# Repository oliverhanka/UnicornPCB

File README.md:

### UnicornPCB
**Unicorn shaped ESP32 and WS2812b board - CTF hardware**

This PCB has been created as a CTF hardware/badge. It features a Wemos D1 style ESP32 as well as 15 WS2812b LEDs, push button and Seeed Studios's Grove Connector for extentability. Power is obtained form the ESP32 board.

#### Hardware
Open Source Hardware

Frontside of the assembled PCB:

Backside of the assembled PCB:

#### Software
Board test firmware included. Requires ESP32 SDK and Arduino NeoPixel library.

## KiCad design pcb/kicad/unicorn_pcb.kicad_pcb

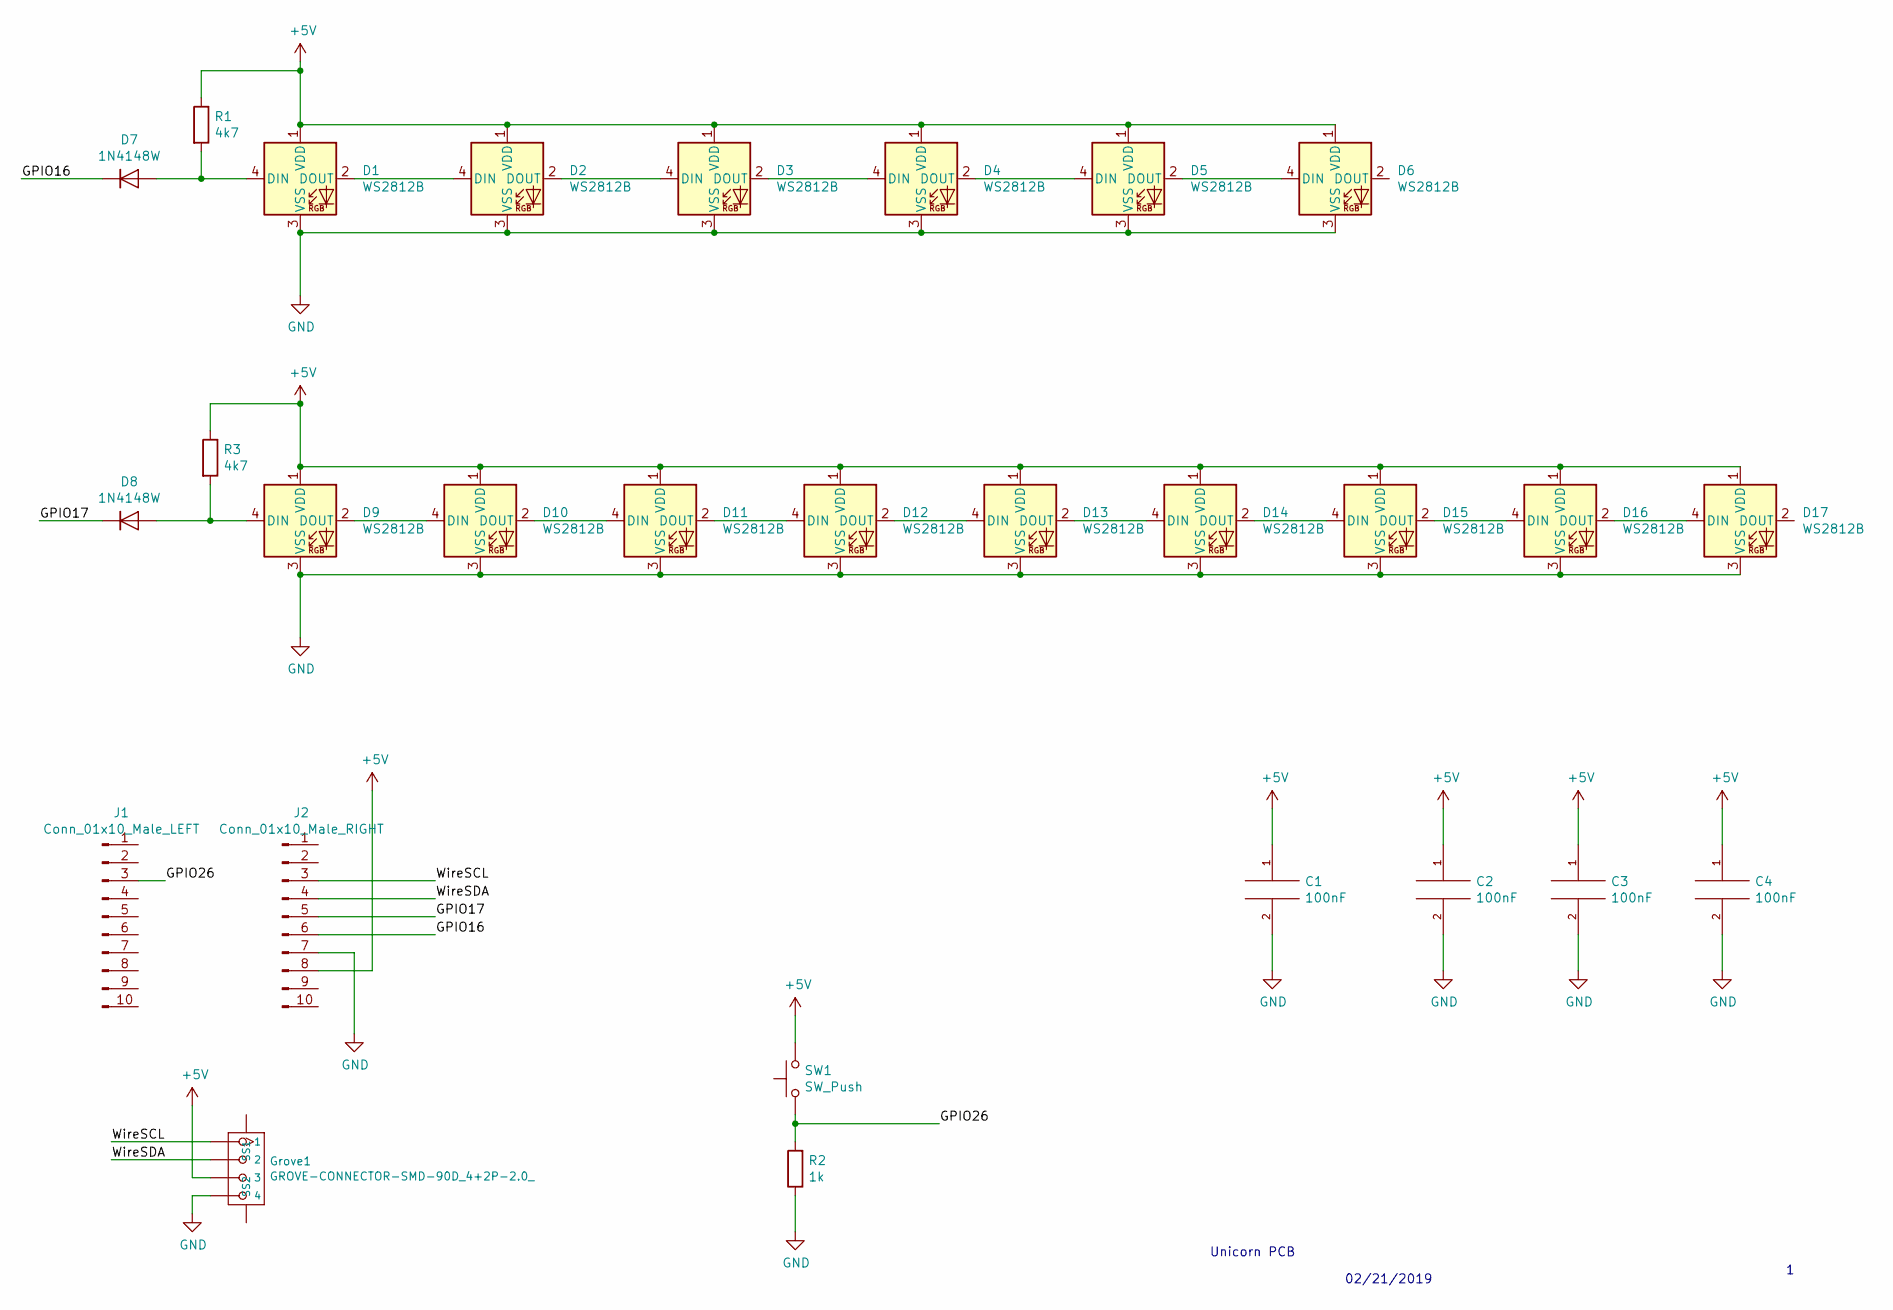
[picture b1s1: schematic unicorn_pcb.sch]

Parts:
C1, C2, C3, C4: 100nF; C_1206_3216Metric_Pad1.42x1.75mm_HandSolder
D1, D2, D3, D4, D5, D6, D9, D10, D11, D12, D13, D14, D15, D16, D17: WS2812B; LED_WS2812B_PLCC4_5.0x5.0mm_P3.2mm
D7, D8: 1N4148W; D_SOD-123
Grove1: GROVE-CONNECTOR-SMD-90D_4+2P-2.0_; grove-SMD-2.0-90D_new
J1: Conn_01x10_Male_LEFT; PinHeader_1x10_P2.54mm_Vertical_SMD_Pin1Right
J2: Conn_01x10_Male_RIGHT; PinHeader_1x10_P2.54mm_Vertical_SMD_Pin1Right
R1, R3: 4k7; R_0805_2012Metric_Pad1.15x1.40mm_HandSolder
R2: 1k; R_0805_2012Metric_Pad1.15x1.40mm_HandSolder
SW1: SW_Push; SW_PUSH_6mm_H5mm

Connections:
+5V: C1.1, C2.1, C3.1, C4.1, D1.1 (VDD), D2.1 (VDD), D3.1 (VDD), D4.1 (VDD), D5.1 (VDD), D6.1 (VDD), D9.1 (VDD), D10.1 (VDD), D11.1 (VDD), D12.1 (VDD), D13.1 (VDD), D14.1 (VDD), D15.1 (VDD), D16.1 (VDD), D17.1 (VDD), Grove1.3, J2.8, R1.1, R3.1, SW1.2
/GPIO16: D7.1 (K), J2.6
/GPIO17: D8.1 (K), J2.5
/GPIO26: J1.3, R2.2, SW1.1
/WireSCL: Grove1.1, J2.3
/WireSDA: Grove1.2, J2.4
GND: C1.2, C2.2, C3.2, C4.2, D1.3 (VSS), D2.3 (VSS), D3.3 (VSS), D4.3 (VSS), D5.3 (VSS), D6.3 (VSS), D9.3 (VSS), D10.3 (VSS), D11.3 (VSS), D12.3 (VSS), D13.3 (VSS), D14.3 (VSS), D15.3 (VSS), D16.3 (VSS), D17.3 (VSS), Grove1.4, J2.7, R2.1
unnamed: D1.2 (DOUT), D2.4 (DIN)
unnamed: D1.4 (DIN), D7.2 (A), R1.2
unnamed: D2.2 (DOUT), D3.4 (DIN)
unnamed: D3.2 (DOUT), D4.4 (DIN)
unnamed: D4.2 (DOUT), D5.4 (DIN)
unnamed: D5.2 (DOUT), D6.4 (DIN)
unnamed: D8.2 (A), D9.4 (DIN), R3.2
unnamed: D10.2 (DOUT), D11.4 (DIN)
unnamed: D9.2 (DOUT), D10.4 (DIN)
unnamed: D11.2 (DOUT), D12.4 (DIN)
unnamed: D12.2 (DOUT), D13.4 (DIN)
unnamed: D13.2 (DOUT), D14.4 (DIN)
unnamed: D14.2 (DOUT), D15.4 (DIN)
unnamed: D15.2 (DOUT), D16.4 (DIN)
unnamed: D16.2 (DOUT), D17.4 (DIN)

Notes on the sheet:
Unicorn PCB
02/21/2019

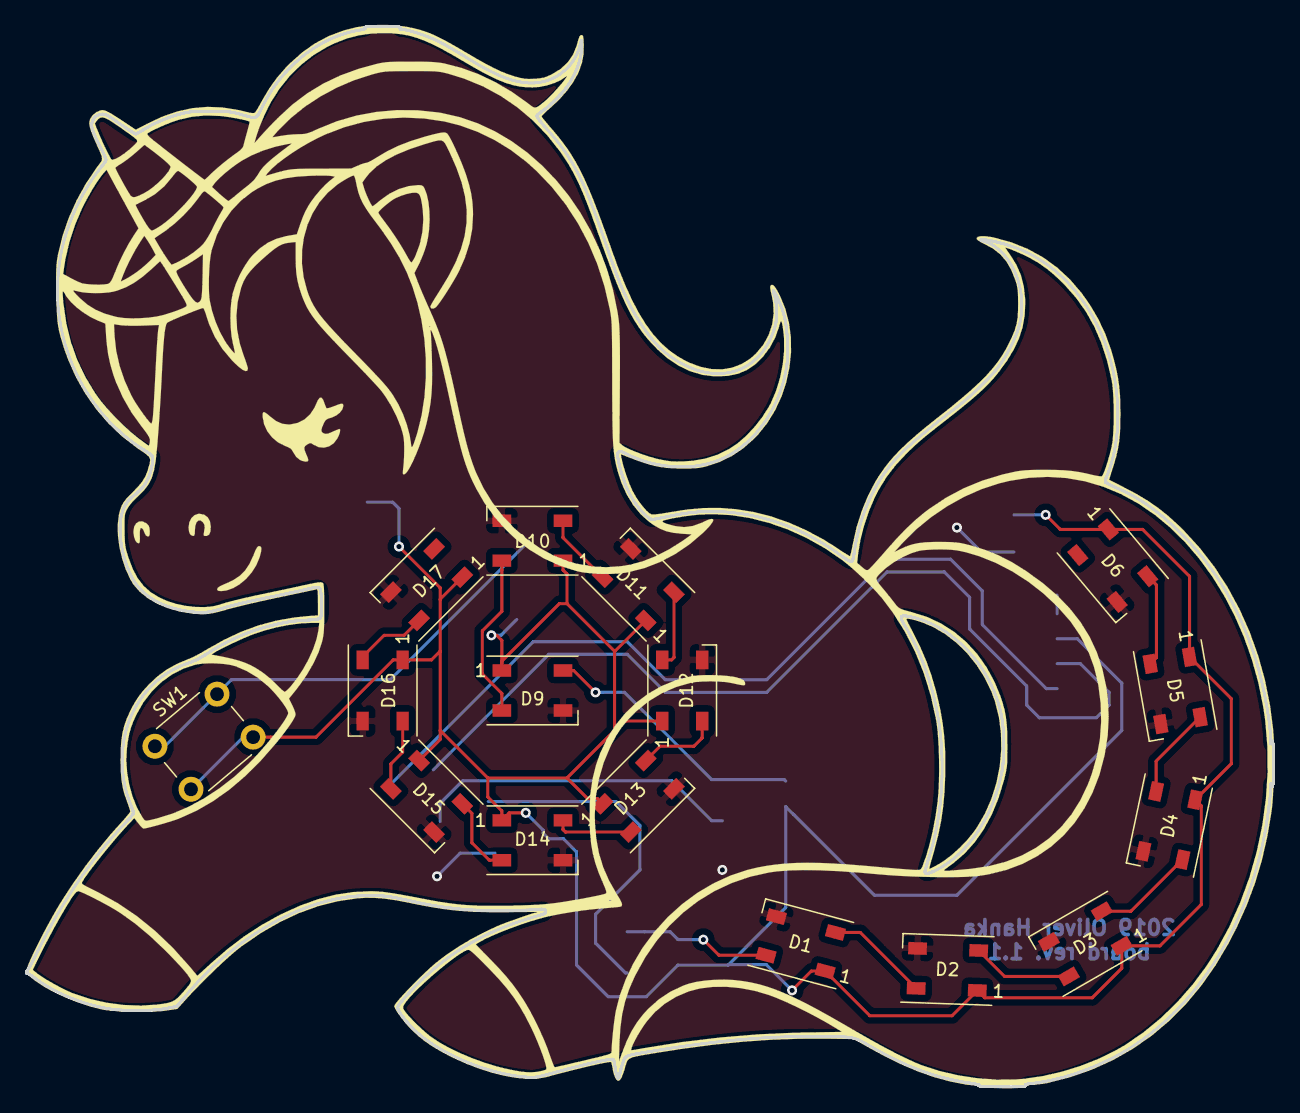
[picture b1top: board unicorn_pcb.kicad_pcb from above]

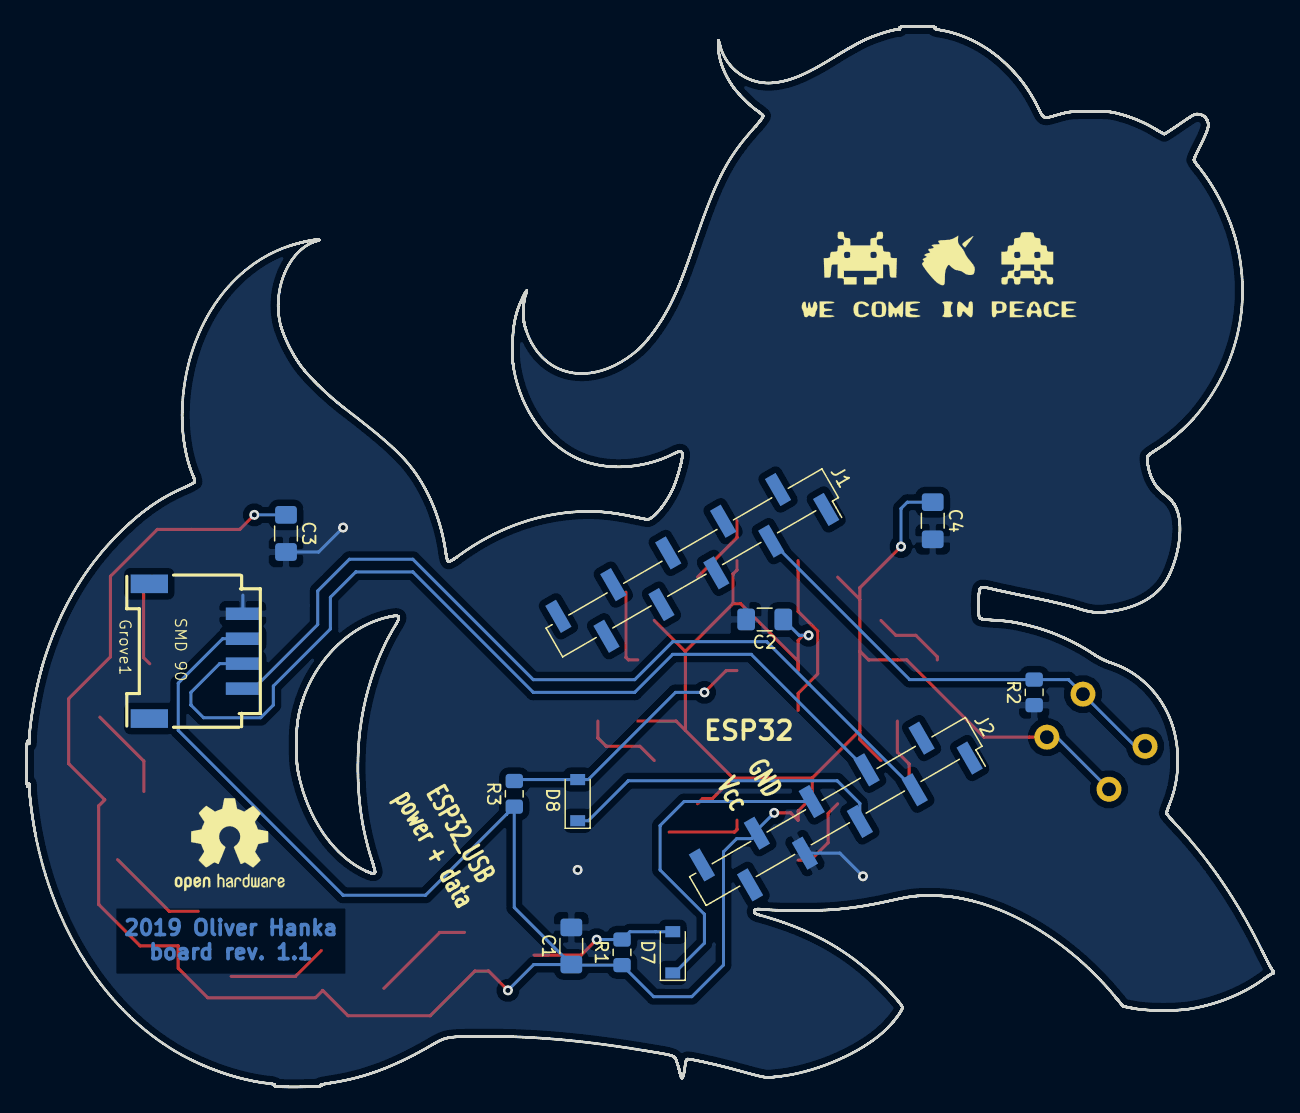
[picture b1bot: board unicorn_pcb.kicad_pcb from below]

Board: 2 copper layers, 100.0 x 85.0 mm, 28 parts (12 on the bottom side), 22 nets.

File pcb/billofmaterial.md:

### Bill of material - Unicorn PCB



| Refernce | Value    |
| -------- | -------- |
| D1-D6    | WS2812b  |
| D7-D8    | 1N4148   |
| D9-D17   | WS2812b  |
| R1, R3   | 4k7      |
| R2.      | 1k       |
| C1-C4    | 100nF    |
| SW1      | SW_push 6x6 |
| Grove1   | Seeed GROVE connector SMD 90 |
| J1       | 1x10 male left SMD alternating |
| J2       | 1x10 male right SMD alternating |
| ESP32    | Wemos D1 style ESP32 board |

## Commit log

2019-04-21 pcb rev 1.1; extended board test firmware
2019-10-06 HW desc PDF added
